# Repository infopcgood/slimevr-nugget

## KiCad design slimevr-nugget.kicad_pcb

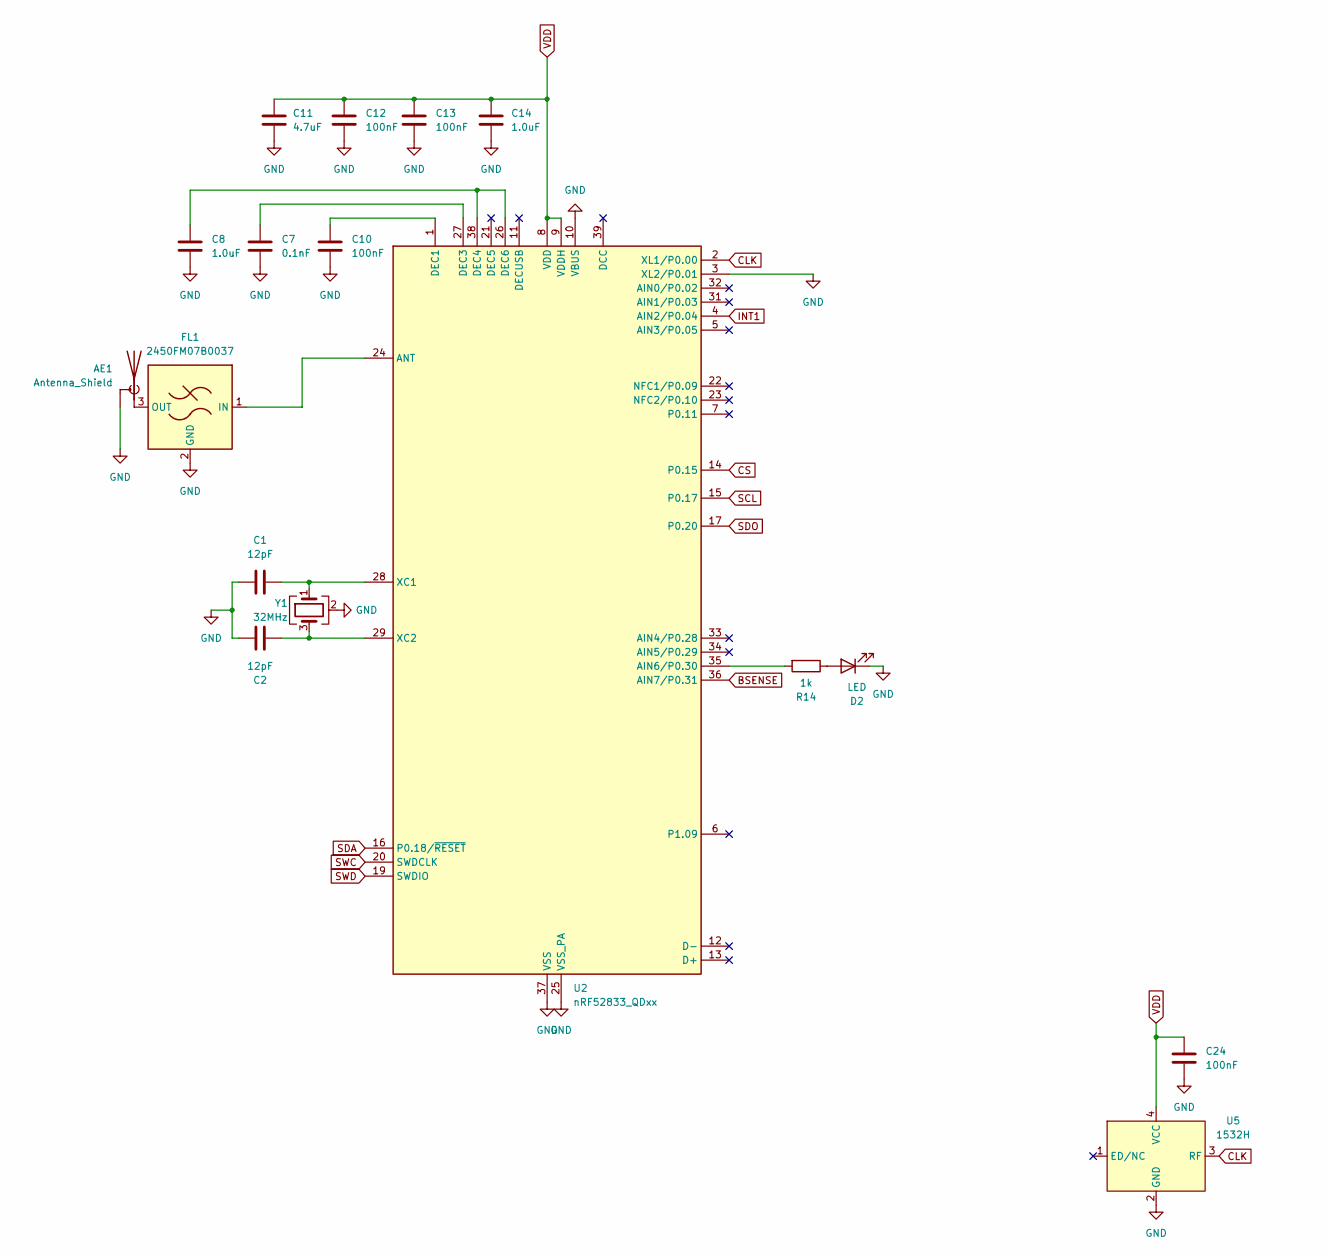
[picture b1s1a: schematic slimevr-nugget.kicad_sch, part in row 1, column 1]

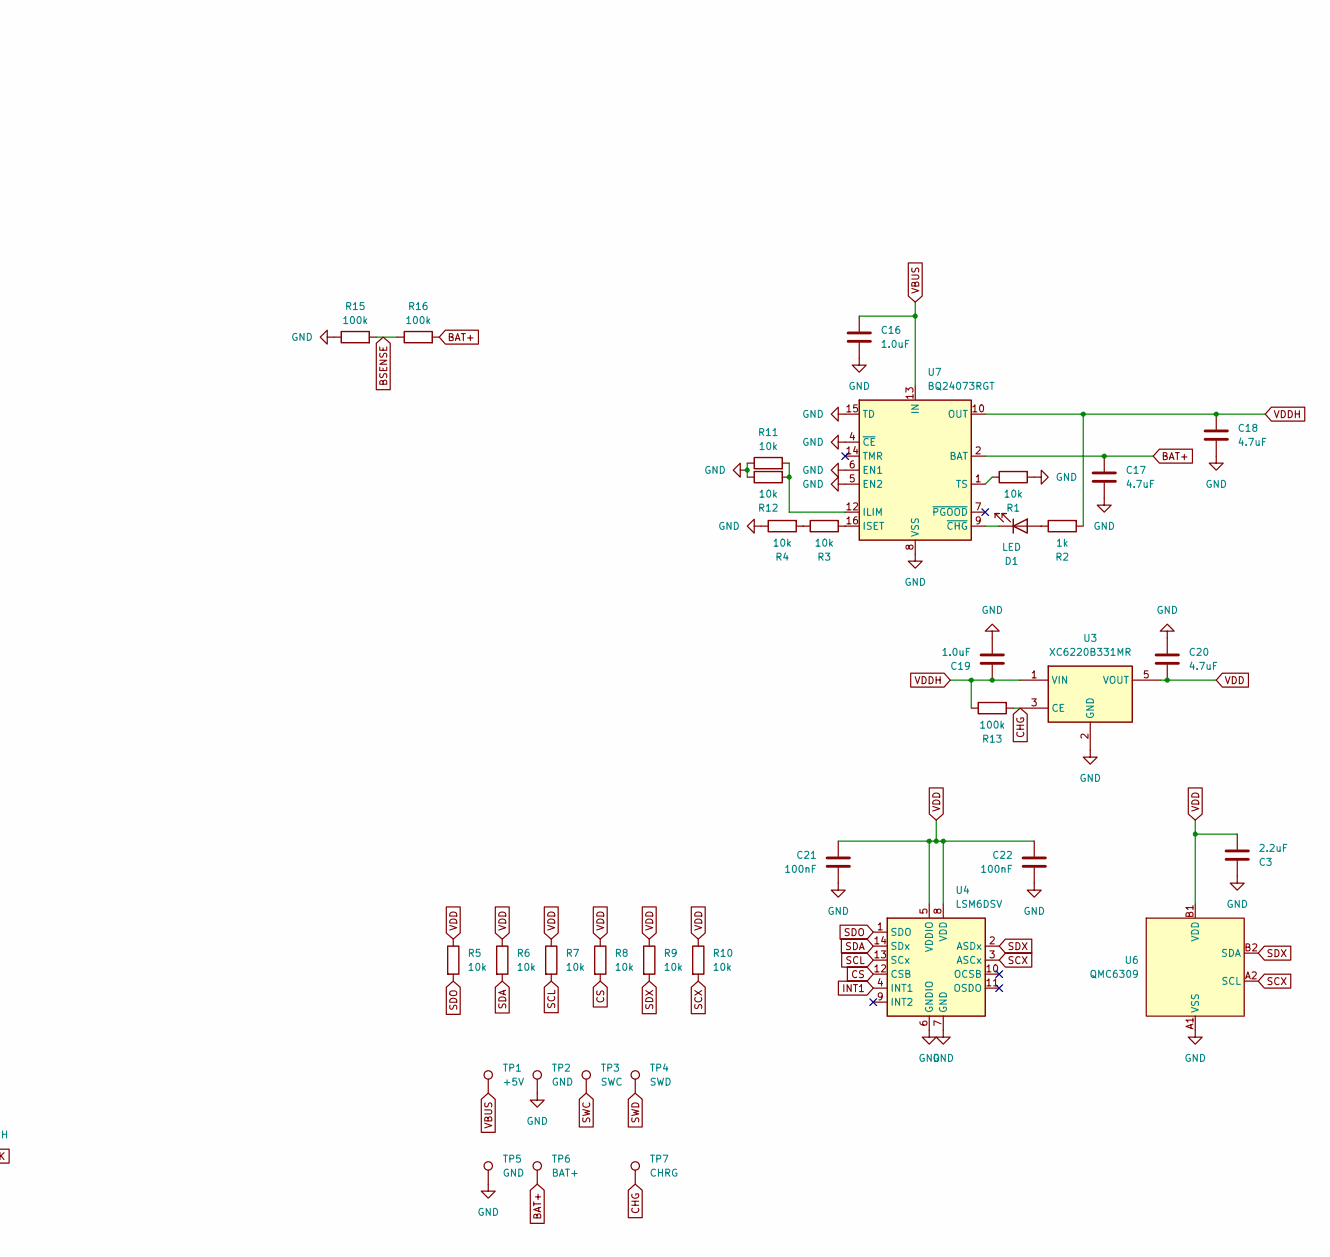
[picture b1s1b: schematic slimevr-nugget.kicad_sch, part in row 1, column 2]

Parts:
AE1: Antenna_Shield; Texas_SWRA117D_2.4GHz_Left
C1, C2: 12pF; C_0402_1005Metric
C3: 2.2uF; C_0402_1005Metric
C7: 0.1nF; C_0402_1005Metric
C8, C14, C16, C19: 1.0uF; C_0402_1005Metric
C10, C12, C13, C21, C22, C24: 100nF; C_0402_1005Metric
C11, C17, C18, C20: 4.7uF; C_0402_1005Metric
D1, D2: LED; LED_0402_1005Metric
FL1: 2450FM07B0037
R1, R3, R4, R5, R6, R7, R8, R9, R10, R11, R12: 10k; R_0402_1005Metric
R2, R14: 1k; R_0402_1005Metric
R13, R15, R16: 100k; R_0402_1005Metric
TP1: +5V; TestPoint_Pad_D1.5mm
TP2: GND; TestPoint_Pad_D1.5mm
TP3: SWC; TestPoint_Pad_D1.5mm
TP4: SWD; TestPoint_Pad_D1.5mm
TP5: GND; TestPoint_Pad_D1.0mm
TP6: BAT+; TestPoint_Pad_D1.0mm
TP7: CHRG; TestPoint_Pad_D1.5mm
U2: nRF52833_QDxx; QFN-40-1EP_5x5mm_P0.4mm_EP3.6x3.6mm
U3: XC6220B331MR; SOT-23-5
U4: LSM6DSV; Bosch_LGA-14_3x2.5mm_P0.5mm
U5: 1532H; Crystal_SMD_3225-4Pin_3.2x2.5mm
U6: QMC6309
U7: BQ24073RGT; VQFN-16-1EP_3x3mm_P0.5mm_EP1.6x1.6mm
Y1: 32MHz; Crystal_SMD_3225-4Pin_3.2x2.5mm

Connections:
BAT+: C17.2, R16.2, TP6.1 (1_1), U7.2 (BAT), U7.3 (BAT)
BSENSE: R15.2, R16.1, U2.36 (AIN7/P0.31)
CHG: R13.2, TP7.1 (1_1), U3.3 (CE)
CLK: U2.2 (XL1/P0.00), U5.3 (RF)
CS: R8.2, U2.14 (P0.15), U4.12 (CSB)
GND: AE1.2 (Shield), C1.1, C2.1, C3.2, C7.1, C8.1, C10.1, C11.1, C12.1, C13.1, C14.1, C16.1, C17.1, C18.1, C19.1, C20.1, C21.1, C22.1, C24.1, D2.1 (K), FL1.2 (GND), FL1.4 (GND), R1.2, R4.1, R11.1, R12.1, R15.1, TP2.1 (1_1), TP5.1 (1_1), U2.3 (XL2/P0.01), U2.10 (VBUS), U2.25 (VSS_PA), U2.37 (VSS), U2.41 (VSS), U3.2 (GND), U4.6 (GNDIO), U4.7 (GND), U5.2 (GND), U6.A1 (VSS), U7.4 (~CE), U7.5 (EN2), U7.6 (EN1), U7.8 (VSS), U7.15 (TD), U7.17 (VSS), Y1.2 (G), Y1.4 (G)
INT1: U2.4 (AIN2/P0.04), U4.4 (INT1)
unnamed: AE1.1 (A), FL1.3 (OUT)
unnamed: D1.2 (A), R2.1
unnamed: D1.1 (K), U7.9 (~CHG)
unnamed: D2.2 (A), R14.1
unnamed: FL1.1 (IN), U2.24 (ANT)
unnamed: R3.1, R4.2
unnamed: R14.2, U2.35 (AIN6/P0.30)
unnamed: C10.2, U2.1 (DEC1)
unnamed: C7.2, U2.27 (DEC3)
unnamed: C8.2, U2.26 (DEC6), U2.38 (DEC4)
unnamed: C1.2, U2.28 (XC1), Y1.1
unnamed: C2.2, U2.29 (XC2), Y1.3
unnamed: R11.2, R12.2, U7.12 (ILIM)
unnamed: R3.2, U7.16 (ISET)
unnamed: R1.1, U7.1 (TS)
SCL: R7.2, U2.15 (P0.17), U4.13 (SCx)
SCX: R10.2, U4.3 (ASCx), U6.A2 (SCL)
SDA: R6.2, U2.16 (P0.18/~RESET), U4.14 (SDx)
SDO: R5.2, U2.17 (P0.20), U4.1 (SDO)
SDX: R9.2, U4.2 (ASDx), U6.B2 (SDA)
SWC: TP3.1 (1_1), U2.20 (SWDCLK)
SWD: TP4.1 (1_1), U2.19 (SWDIO)
VBUS: C16.2, TP1.1 (1_1), U7.13 (IN)
VDD: C3.1, C11.2, C12.2, C13.2, C14.2, C20.2, C21.2, C22.2, C24.2, R5.1, R6.1, R7.1, R8.1, R9.1, R10.1, U2.8 (VDD), U2.9 (VDDH), U2.18 (VDD), U2.30 (VDD), U2.40 (VDD), U3.5 (VOUT), U4.5 (VDDIO), U4.8 (VDD), U5.4 (VCC), U6.B1 (VDD)
VDDH: C18.2, C19.2, R2.2, R13.1, U3.1 (VIN), U7.10 (OUT), U7.11 (OUT)

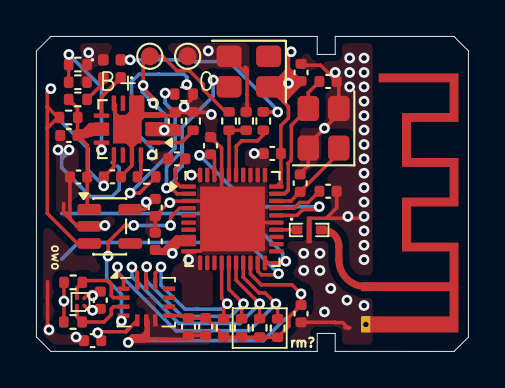
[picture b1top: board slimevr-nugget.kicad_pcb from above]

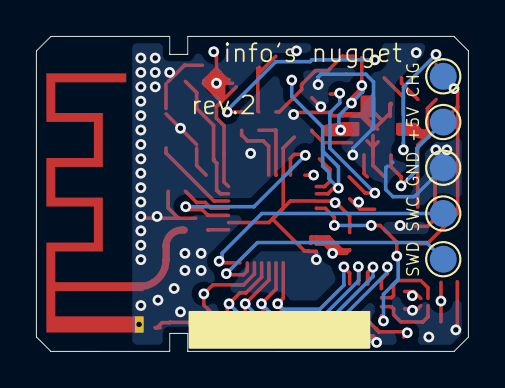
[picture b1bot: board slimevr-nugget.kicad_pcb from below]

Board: 4 copper layers, 24.0 x 17.5 mm, 52 parts (5 on the bottom side), 32 nets.

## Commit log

2026-03-04 Base design for nRF52840-QFAA
2026-03-04 Add power path circuit
2026-03-04 Add Mumo as submodule
2026-03-05 Add rest of ICs (routing unfinished)
2026-03-06 Complete circuit and routing
2026-04-16 Revision 2
2026-04-19 Turn off system by pulling down CE of LDO while charging
2026-04-20 Final production version
2026-04-27 Add CERN-OHL-S v2 license
2026-04-29 Add 1:1 battery sensing circuit
2026-04-30 Change to nRF52833, swap antenna matching circuit to IC
2026-04-30 Impedance match 2.4GHz trace
